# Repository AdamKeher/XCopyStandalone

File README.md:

# XCopy Standalone
An Arduino / Teensy based version of the Amiga XCopy application for copying floppy disks to and from ADF files. Built for the Teensy 3.2 using a custom PCB and an unmodified PC 3.5" floppy disk drive.

### Note
XCopy Standalone liberally uses floppy interface code taken from the excelent and generously open source ADF-Copy by Dominik Tonn. 
https://nickslabor.niteto.de/download/
Nicks software uses usb serial and a Java client or a MTP connection via usb to transfer data. XCopy Standalone focuses on a standalone unit using SD card storage and a LCD and / or web sockets interface for control.

### Thanks
Special thanks to Giants for all his help with this version including web interface graphics, documentation, suggestions etc.

## Device

## Status
This project is under heavy development and is in a state of flux with new hardware and software being actively worked on. The firmware version lives in `src/XCopy/XCopy.h`; this README describes v743.26.

## New Features - 09/2026

Since the 04/2023 release the device has grown a flux layer under the copier, a
second file system layer over the SD card, and a rebuilt web interface.

* **Disk Info** - a track analyser that describes what is on a disk rather than
  copying it. One pass per track, no retries, so a protected track with the wrong
  cylinder in its headers, a track with no sectors at all, or a disk with 84
  cylinders instead of 80 is the output rather than an error. Draws both surfaces
  as disks, a flux interval histogram per track, an angular track view you can
  point at, and the decoded sector under the pointer. Runs against the drive, or
  replays an SCP image through the same decoder.
* **Drive Toolkit** - a bench instrument for bringing up an unknown drive. Every
  interface line sampled with state, counts and rates; the safe outputs drivable
  one at a time, so a drive can be provoked into saying which fault it has; and a
  continuous head calibration read, after Amiga Test Kit's, that reports how many
  of the eleven sectors came back clean and whether the ones that did not came
  from the cylinder either side. Write data and write enable are deliberately not
  exposed.
* **SuperCard Pro flux images** - `readscp` captures a disk to an SCP file,
  streamed a block at a time because a single DD revolution is larger than the RAM
  on the whole part. A matching reader replays one back through the analyser.
* **Live USB flux streaming** - `live` hands the USB session to a host that does
  its own decoding, with non blocking in band seeking so the capture ring is still
  draining during a head move. Host side probe in `files/Tools/xcopylive_probe.py`.
* **ADF images as volumes** - mount ADF files as `ADF0:` and `ADF1:`, and the disk
  in the drive itself as `DF0:`, then use `dir`, `cat`, `cp`, `mkdir` and `rm`
  across the card and any mounted image. Mounts are read only unless asked
  otherwise. ADFlib upgraded to 0.10.7, with drivers rather than local edits.
* **New serial console** - a table driven interpreter with grouped help, per
  command options, tab completion and history, in place of the hand written parser.
* **Rebuilt web interface** - six tabs over one set of shared tokens and
  components, with the Disk Monitor histogram and the Disk Info analysis streamed
  to the browser as they are produced rather than gathered first.
* **Over the air updates** - firmware and web assets over Wi-Fi, no cable needed.
* **A name on the network** - the device calls itself `xcopy` to DHCP, to mDNS and
  to OTA.
* **Host side tests** - the `native` and `native_adf` environments run the file
  system and console tests off the board.

## New Features - 04/2023
* v0.19 PCB released with intergrated ESP8266 for WiFi
  * Moved to Kicad from Eagle
  * Changed SD Card to MicroSD reader
  * Added WiFi
  * Connected USB serial to Teensy USB serial
  * Moved TFT to cheap chinese Adafruit knock off, this has changed the pinout
    * https://www.aliexpress.com/item/4001144194129.html
    * USD $1.89!
  * Moved navigation stick to cheap chinese item from LCSC
  * Additional 3.3v power regulator to relieve Teensy's
  * Added larger electrolytic cap for floppy power
  * Switced to four layer board as they are cheap and provide better power / ground planes
* Project code moved from Arduino to ProjectIO with all libraries preinstalled
* New web interface
* Amiga module ripper
* Bootblock library / virus checker using brainfile format
* Web based disk monitor
* Network NTP time update
* Upload and download ADF files via web interface

## Features
* Software
  * Disk copy
    * Disk to SD Card
    * SD Card to Disk
    * Disk to Disk
    * Disk to Temporary Flash
    * Temporary Flash to Disk
  * Flux
    * Read a disk to a SuperCard Pro (SCP) flux image
    * Analyse a disk, or an SCP image, track by track
    * Flux interval histograms, per track and live during a copy
    * Stream a live drive to a host over USB for off board decoding
  * File systems
    * Amiga file system support for floppy disks and ADF files via ADFlib 0.10.7
    * Mount ADF images as `ADF0:` / `ADF1:`, and the disk in the drive as `DF0:`
    * List, print, copy, make and remove across the card and mounted images
  * Drive diagnostics
    * Every interface line sampled, with state, counts and rates
    * Individually drivable outputs for provoking a fault out of a drive
    * Continuous head calibration read with a live per cylinder tally
    * Drive speed from the index
  * Test disk
  * Format disk
  * Search a disk for case sensitive ascii text, or for tracker modules
  * Amiga module ripper
  * Bootblock library / virus checker using brainfile format
  * Serial command line, table driven, with tab completion and history
  * Interfaces
    * TFT LCD
    * USB Serial
    * HTML over WebSockets
  * Network
    * Over the air firmware and web asset updates
    * NTP time update and time zone
    * Announces itself as `xcopy` to DHCP, mDNS and OTA
  * Serial passthrough for programming onboard ESP8266
* Hardware
  * IDC 34 pin standard floppy drive cable interface
  * 1.8" ST7735R 128x160, 18bit color LCD
  * 5 way navigation joystick
  * Mono PAM8302 amplifier with adjustable Pot
    * Onboard mounted speaker
  * SD Card reader
  * 128MBit Flash Rom with built in ADF files
  * CR1220 battery backed realtime clock
  * ESP8266 for websockets driven interface
  * Single USB plug for serial and to power floppy and Teensy 3.2
  * Status LED's
  * Additional 3.3v power regulator
  * Gerbers, schematic and pcb layout files available 

# PCB

# Web Interface

Six tabs over one WebSocket connection to the ESP8266. The footer carries the
signal strength, the link state and what the device is doing, on every tab.

### Disk Copy

Every copy path in one place - between the drive, the SD card, the onboard flash,
and an ADF or SCP file on the card - over a live track map of both surfaces and a
rolling flux view of the track being read.

### Disk Monitor

A sector at a time: the decoded header, a hex dump, an ascii dump in either the
browser font or the Amiga one, and the track's flux histogram. Below them a block
scan of the whole disk, with ascii and tracker module searches, and blocks that
can be selected and written out to the card.

### Disk Info

The analyser. Both surfaces drawn as disks with every sector coloured by what was
found there, a status panel for the selected track, an angular track view of the
raw cell stream against the sectors decoded out of it, the flux histogram, and the
decoded sector under the pointer.

### Drive Toolkit

The drive itself rather than the disk in it. Sampled interface lines down the
left, the calibration read across the top, and a session tally that accumulates
per cylinder and head - so an intermittent read shows up as intermittent rather
than as one bad pass.

### SD Card

The contents of the card, with upload and download.

### Log

The serial console in the browser - the same interpreter, the same commands and
the same output as the USB port.

# Build Environment Notes:

## VSCode Plugins:
1. PlatoformIO with Teensy & ESP8266 board 
2. Todo+ v4.18.4 by Fabio Spampinato

* Xcopy.h contains PCBVERSION define to target firmware builds to different PCB versions

## ESP8266 Build Notes:
1. Select the `d1_mini` environment (both boards are environments of this one project)
2. Plugin XCopyStandalone device and select "Debugging >> ESP >> ESP Programming Mode"
3. Set serial port to the Teensy port, the device will passthrough serial data to the ESP8266 program
4. Upload code, then upload the web assets with the `d1_mini` "Build Filesystem Image" and "Upload Filesystem Image" tasks

### Over the air

Once the ESP is on your network it can be updated over Wi-Fi instead, using the
`d1_mini_ota` environment - both the firmware and the web assets:

```shell
pio run -e d1_mini_ota -t upload      # firmware
pio run -e d1_mini_ota -t uploadfs    # web interface
pio run -e d1_mini_ota -t uploadall   # both, firmware first
```

`uploadall` is a task of this project rather than of PlatformIO, and it waits
between the two because each upload reboots the ESP.

Use `uploadfs` for the web assets, not `uploadfsota`. The platform decides
whether espota is offering a sketch or a filesystem image by matching the target
name exactly, and `uploadfsota` misses that test - so the image goes over as a
sketch, is measured against the 1MB sketch region instead of its own 2MB
partition, and is refused with `ERROR[4]: Not Enough Space`. `scripts/
espota_fs_flag.py` puts the missing flag back, so both targets now work.

The device calls itself `xcopy` to the DHCP server, to mDNS and to OTA, so it is
reachable by whichever name your network gives it. `upload_port` in
`platformio.ini` is set to `xcopy.lab` - change it to `xcopy.local` to go via
mDNS instead, or to a bare IP address if neither resolves from your machine.

The serial passthrough above is unchanged and remains the way back in if an
update ever leaves the ESP unable to join a network.
5. Select "Debugging >> ESP >> Reset ESP"
6. Open a serial terminal
7. Connect to your wireless access point using the connect command
```shell
>> connect SSIDName Password
```
8. Type the following commands to confirm you have connected
```shell
>> status
WiFi Status: Connected
-----
Mode: STA
PHY mode: N
Channel: 10
AP id: 0
Status: 5
Auto connect: 1
SSID (6): SSIDName
Passphrase (12): Password
BSSID set: 0
>> ip
192.168.X.XX
>> ssid
SSIDName
>>
```

## Project layout

Both firmwares are environments of a single PlatformIO project, so the IDE lists
them in one Project Tasks tree and `pio run` with no arguments builds the pair.

| | |
|---|---|
| `src/` | Teensy 3.2 firmware, built by the `teensy31` environment |
| `src/esp8266/` | ESP8266 firmware, built by the `d1_mini` environment |
| `esp8266/data/` | web interface, uploaded to the ESP as a LittleFS image |
| `shared/` | the Teensy to ESP link contract, compiled into both |
| `lib/` | libraries for both; `esp8266/lib/` holds the ESP only ones |

Both boards are environments of the one project: `teensy31`, `d1_mini`, and
`d1_mini_ota` for updating the ESP over Wi-Fi. Two more, `native` and
`native_adf`, build nothing for a board and exist to run the console and file
system tests on the host.

Neither firmware is a `.ino` sketch: PlatformIO only converts a sketch sitting at
the top of the source directory, and with two source trees neither one can be.

## How to build PlatformIO based project

1. [Install PlatformIO Core](http://docs.platformio.org/page/core.html)
2. Download [development platform with examples](https://github.com/platformio/platform-teensy/archive/develop.zip)
3. Open the project
4. Pick the environment you want - `teensy31` or `d1_mini` - or build both at once
5. Select 'PlatformIO:Build'
6. Select 'PlatformIO:Upload'

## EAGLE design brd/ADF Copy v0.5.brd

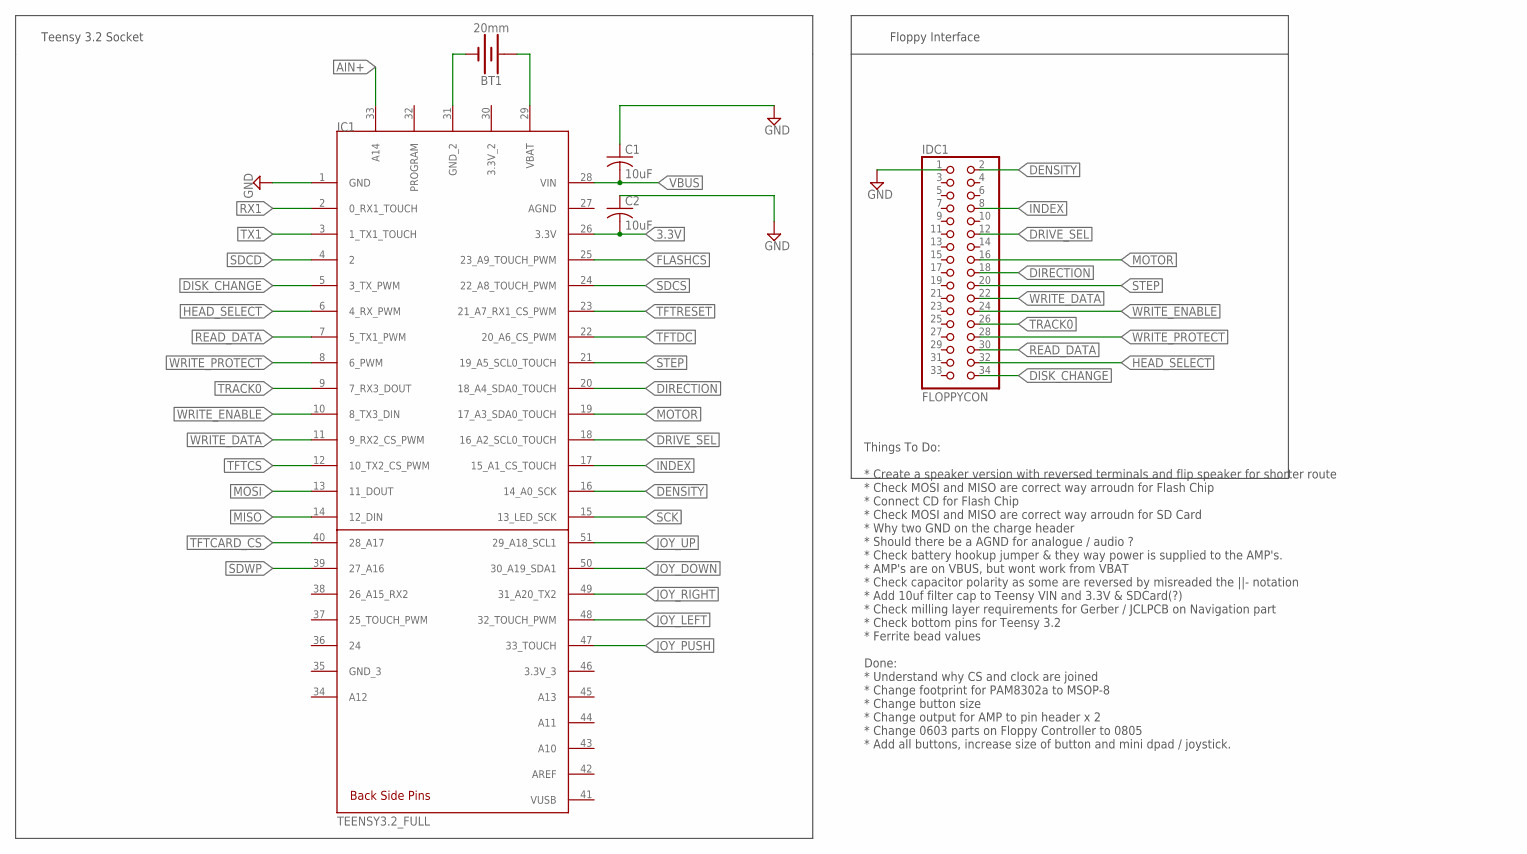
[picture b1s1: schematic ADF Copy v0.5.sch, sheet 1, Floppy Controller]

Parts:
BT1: 20mm; BATTCOM_20MM_PTH
C1, C2: 10uF; C0805
IC1: TEENSY3.2_FULL; DIP28X4-2.54-34.7X15.24MM
IDC1: FLOPPYCON; 2X17/90

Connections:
3.3V: C2.2, IC1.26 (3.3V); also elsewhere on the board
AIN+: IC1.33 (A14); also elsewhere on the board
DENSITY: IC1.16 (14_A0_SCK), IDC1.2
DIRECTION: IC1.20 (18_A4_SDA0_TOUCH), IDC1.18
DISK_CHANGE: IC1.5 (3_TX_PWM), IDC1.34
DRIVE_SEL: IC1.18 (16_A2_SCL0_TOUCH), IDC1.12
FLASHCS: IC1.25 (23_A9_TOUCH_PWM); also elsewhere on the board
GND: C1.1, C2.1, IC1.1 (GND), IDC1.1; also elsewhere on the board
HEAD_SELECT: IC1.6 (4_RX_PWM), IDC1.32
INDEX: IC1.17 (15_A1_CS_TOUCH), IDC1.8
JOY_DOWN: IC1.50 (30_A19_SDA1); also elsewhere on the board
JOY_LEFT: IC1.48 (32_TOUCH_PWM); also elsewhere on the board
JOY_PUSH: IC1.47 (33_TOUCH); also elsewhere on the board
JOY_RIGHT: IC1.49 (31_A20_TX2); also elsewhere on the board
JOY_UP: IC1.51 (29_A18_SCL1); also elsewhere on the board
MISO: IC1.14 (12_DIN); also elsewhere on the board
MOSI: IC1.13 (11_DOUT); also elsewhere on the board
MOTOR: IC1.19 (17_A3_SDA0_TOUCH), IDC1.16
unnamed: BT1.2 (-), IC1.31 (GND_2)
unnamed: BT1.1 (+), IC1.29 (VBAT)
READ_DATA: IC1.7 (5_TX1_PWM), IDC1.30
RX1: IC1.2 (0_RX1_TOUCH); also elsewhere on the board
SCK: IC1.15 (13_LED_SCK); also elsewhere on the board
SDCD: IC1.4 (2); also elsewhere on the board
SDCS: IC1.24 (22_A8_TOUCH_PWM); also elsewhere on the board
SDWP: IC1.39 (27_A16); also elsewhere on the board
STEP: IC1.21 (19_A5_SCL0_TOUCH), IDC1.20
TFTCARD_CS: IC1.40 (28_A17); also elsewhere on the board
TFTCS: IC1.12 (10_TX2_CS_PWM); also elsewhere on the board
TFTDC: IC1.22 (20_A6_CS_PWM); also elsewhere on the board
TFTRESET: IC1.23 (21_A7_RX1_CS_PWM); also elsewhere on the board
TRACK0: IC1.9 (7_RX3_DOUT), IDC1.26
TX1: IC1.3 (1_TX1_TOUCH); also elsewhere on the board
VBUS: C1.2, IC1.28 (VIN); also elsewhere on the board
WRITE_DATA: IC1.11 (9_RX2_CS_PWM), IDC1.22
WRITE_ENABLE: IC1.10 (8_TX3_DIN), IDC1.24
WRITE_PROTECT: IC1.8 (6_PWM), IDC1.28

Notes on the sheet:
Teensy 3.2 Socket
Things To Do: * Create a speaker version with reversed terminals and flip speaker for shorter route * Check MOSI and MISO are correct way arroudn for Flash Chip * Connect CD for Flash Chip * Check MOSI and MISO are correct way arroudn for SD Card * Why two GND on the charge header * Should there be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
Floppy Interface

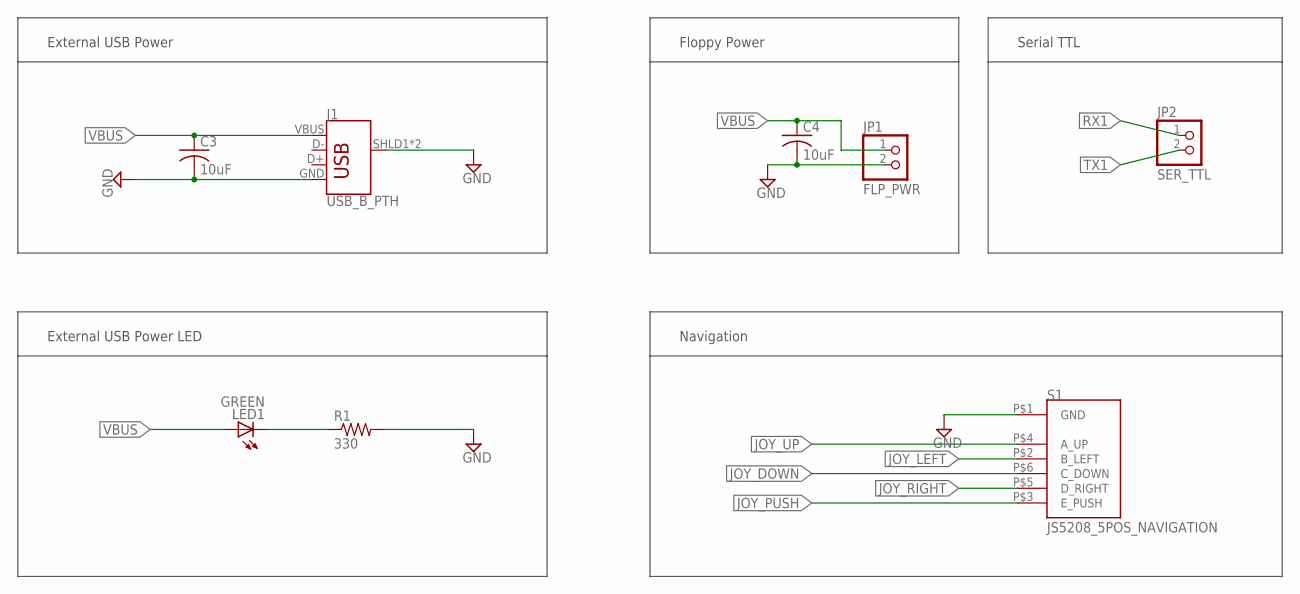
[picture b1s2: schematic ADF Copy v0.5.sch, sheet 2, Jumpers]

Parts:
C3, C4: 10uF; C0805
J1: USB_B_PTH; USB-B-PTH
JP1: FLP_PWR; 1X02
JP2: SER_TTL; 1X02
LED1: GREEN; CHIP-LED0805
R1: 330; R0805
S1: JS5208_5POS_NAVIGATION

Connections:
GND: C3.2, C4.2, J1.GND, J1.SHLD1 (SHIELD), J1.SHLD2 (SHIELD), JP1.2, R1.2, S1.P$1 (GND); also elsewhere on the board
JOY_DOWN: S1.P$6 (C_DOWN); also elsewhere on the board
JOY_LEFT: S1.P$2 (B_LEFT); also elsewhere on the board
JOY_PUSH: S1.P$3 (E_PUSH); also elsewhere on the board
JOY_RIGHT: S1.P$5 (D_RIGHT); also elsewhere on the board
JOY_UP: S1.P$4 (A_UP); also elsewhere on the board
unnamed: LED1.C, R1.1
RX1: JP2.1; also elsewhere on the board
TX1: JP2.2; also elsewhere on the board
VBUS: C3.1, C4.1, J1.VBUS, JP1.1, LED1.A; also elsewhere on the board

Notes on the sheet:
Serial TTL
Floppy Power
External USB Power
External USB Power LED
Navigation

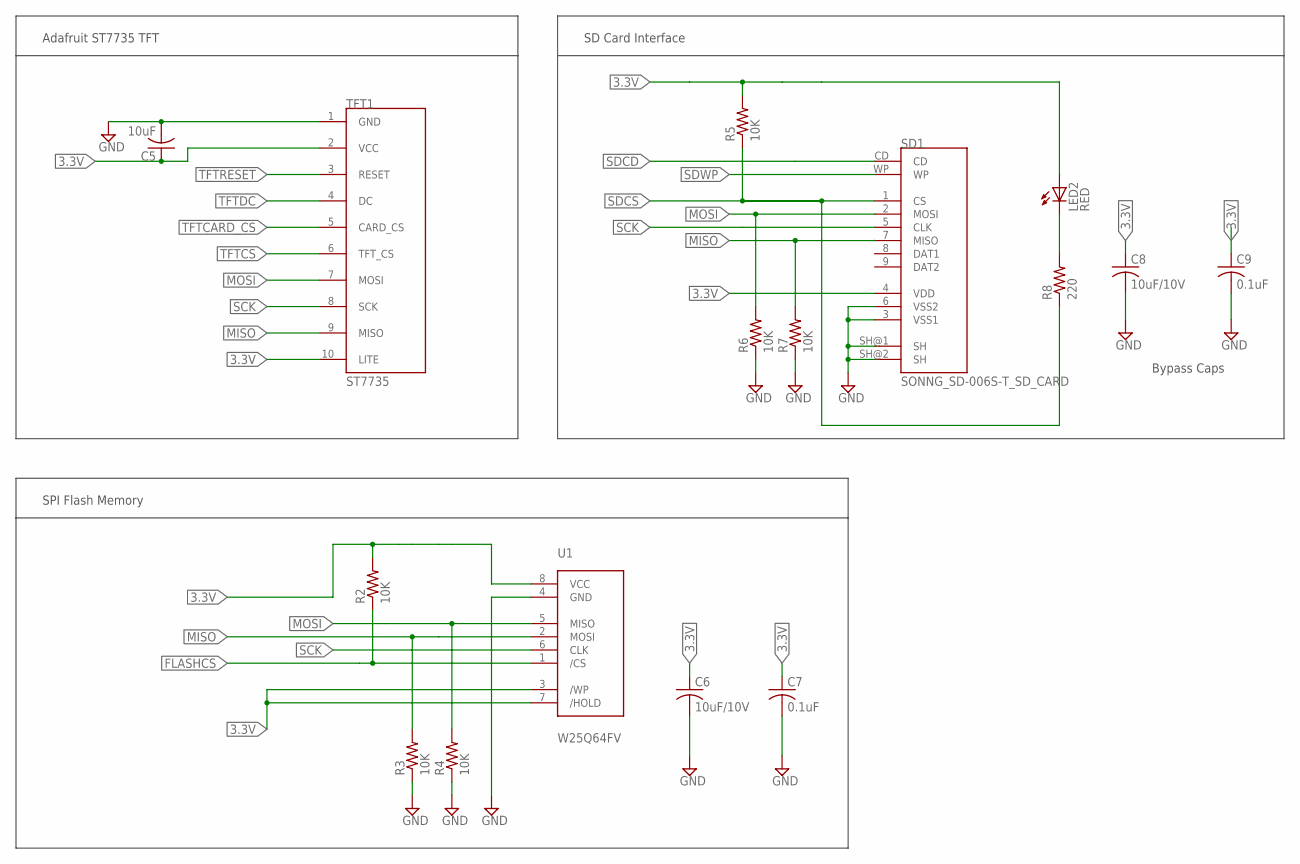
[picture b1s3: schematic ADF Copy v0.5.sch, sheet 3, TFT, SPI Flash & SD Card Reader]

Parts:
C5: 10uF; C0805
C6, C8: 10uF/10V; C0805
C7, C9: 0.1uF; C0805
LED2: RED; CHIP-LED0805
R2, R3, R4, R5, R6, R7: 10K; R0805
R8: 220; R0805
SD1: SONNG_SD-006S-T_SD_CARD; SD-006S-T
TFT1: ST7735
U1: W25Q64FV; SOIC8

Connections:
3.3V: C5.1, C6.1, C7.1, C8.1, C9.1, LED2.A, R2.2, R5.2, SD1.4 (VDD), TFT1.2 (VCC), TFT1.10 (LITE), U1.3 (/WP), U1.7 (/HOLD), U1.8 (VCC); also elsewhere on the board
FLASHCS: R2.1, U1.1 (/CS); also elsewhere on the board
GND: C5.2, C6.2, C7.2, C8.2, C9.2, R3.1, R4.1, R6.1, R7.1, SD1.3 (VSS1), SD1.6 (VSS2), SD1.SH@1 (SH), SD1.SH@2 (SH), TFT1.1 (GND), U1.4 (GND); also elsewhere on the board
MISO: R3.2, R7.2, SD1.7 (MISO), TFT1.9 (MISO), U1.2 (MOSI); also elsewhere on the board
MOSI: R4.2, R6.2, SD1.2 (MOSI), TFT1.7 (MOSI), U1.5 (MISO); also elsewhere on the board
unnamed: LED2.C, R8.2
SCK: SD1.5 (CLK), TFT1.8 (SCK), U1.6 (CLK); also elsewhere on the board
SDCD: SD1.CD; also elsewhere on the board
SDCS: R5.1, R8.1, SD1.1 (CS); also elsewhere on the board
SDWP: SD1.WP; also elsewhere on the board
TFTCARD_CS: TFT1.5 (CARD_CS); also elsewhere on the board
TFTCS: TFT1.6 (TFT_CS); also elsewhere on the board
TFTDC: TFT1.4 (DC); also elsewhere on the board
TFTRESET: TFT1.3 (RESET); also elsewhere on the board

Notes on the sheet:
Adafruit ST7735 TFT
SD Card Interface
Bypass Caps
SPI Flash Memory

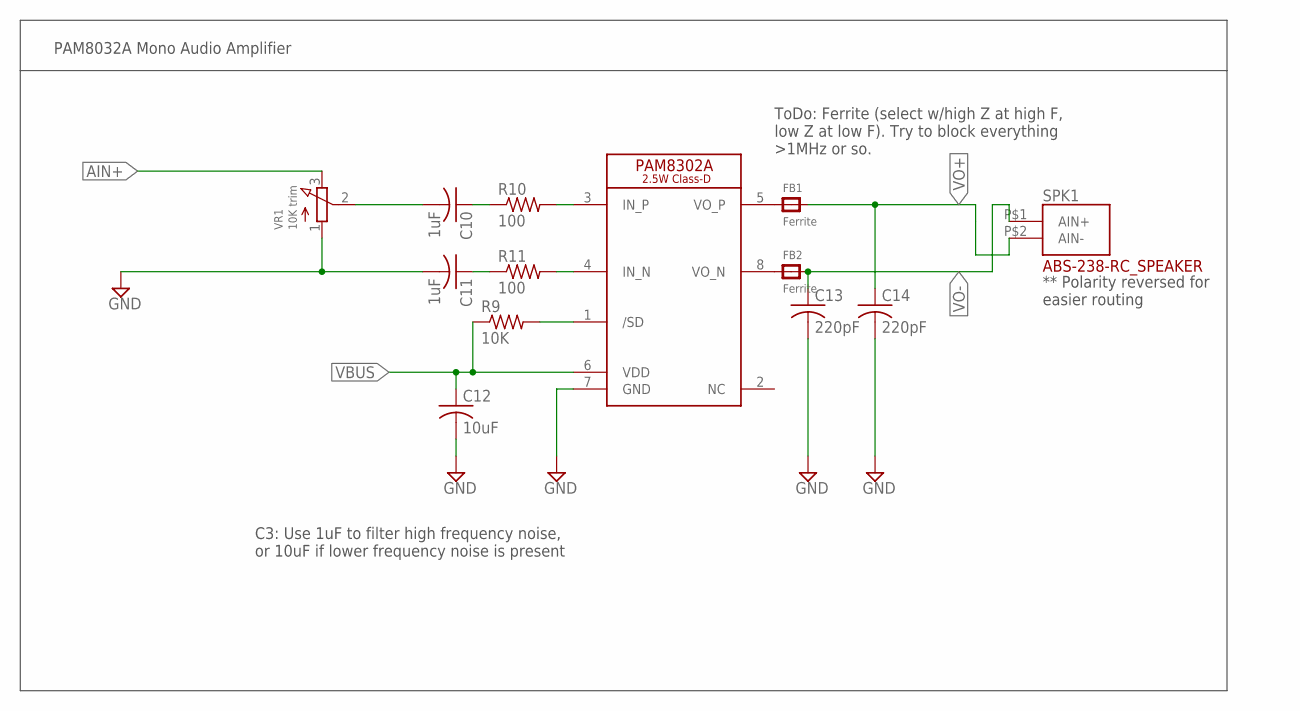
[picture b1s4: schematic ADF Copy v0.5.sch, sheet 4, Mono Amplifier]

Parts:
C10, C11: 1uF; C0805
C12: 10uF; C0805
C13, C14: 220pF; C0805
FB1, FB2: Ferrite; _0805
IC2: PAM8302A; SOIC8
R9: 10K; R0805
R10, R11: 100; R0805
SPK1: ABS-238-RC_SPEAKER
VR1: 10K trim; TRIMPOT_BOURNS_3303W

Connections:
AIN+: VR1.3 (E); also elsewhere on the board
GND: C11.2, C12.2, C13.2, C14.2, IC2.7 (GND), VR1.1 (A); also elsewhere on the board
unnamed: IC2.1 (/SD), R9.2
unnamed: FB1.1, IC2.5 (VO_P)
unnamed: FB2.1, IC2.8 (VO_N)
unnamed: IC2.4 (IN_N), R11.2
unnamed: IC2.3 (IN_P), R10.2
unnamed: C11.1, R11.1
unnamed: C10.1, R10.1
unnamed: C10.2, VR1.2 (S)
VBUS: C12.1, IC2.6 (VDD), R9.1; also elsewhere on the board
VO+: C14.1, FB1.2, SPK1.P$2 (AIN-)
VO-: C13.1, FB2.2, SPK1.P$1 (AIN+)

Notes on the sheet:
ToDo: Ferrite (select w/high Z at high F, low Z at low F). Try to block everything >1MHz or so.
C3: Use 1uF to filter high frequency noise, or 10uF if lower frequency noise is present
PAM8032A Mono Audio Amplifier
** Polarity reversed for easier routing

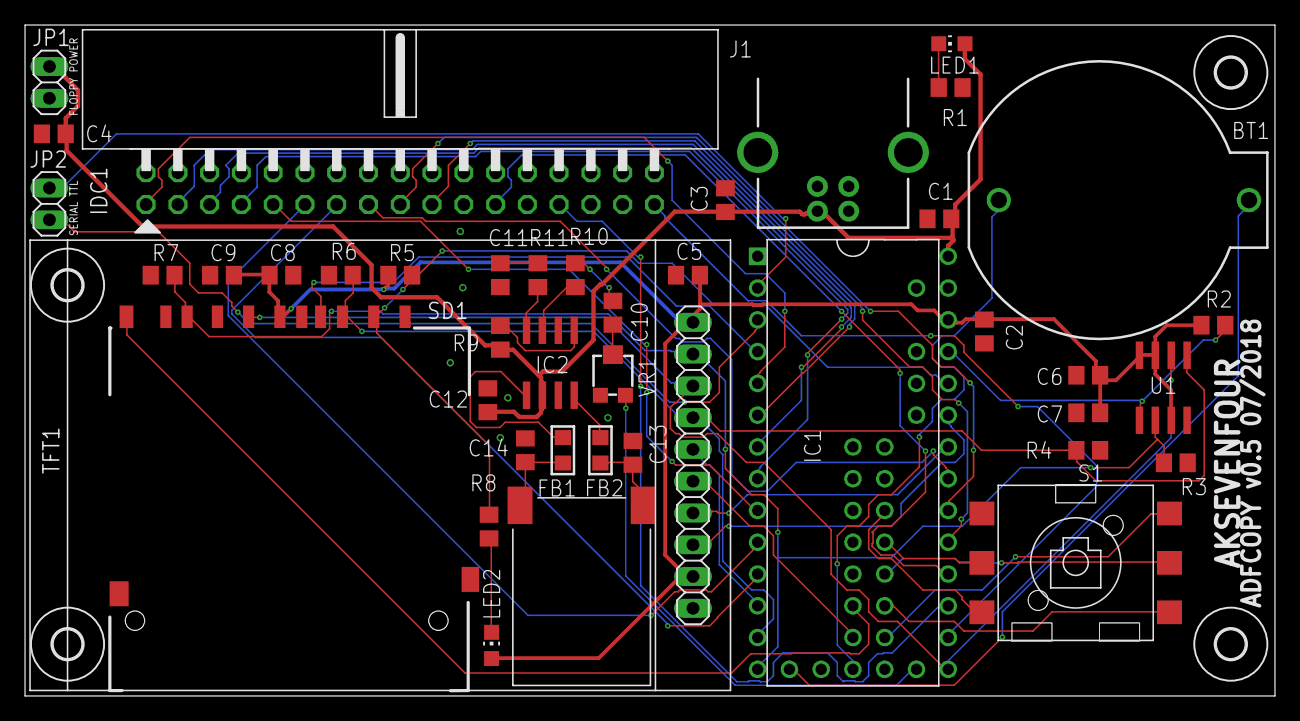
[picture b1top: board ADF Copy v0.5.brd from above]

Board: 2 copper layers, 99.9 x 53.6 mm, 46 parts (0 on the bottom side), 49 nets.

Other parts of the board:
U$1, U$2, U$3, U$4: M2_HOLE

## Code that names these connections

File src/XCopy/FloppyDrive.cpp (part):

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    registerSetup(1);
    pinMode(_dens, OUTPUT);
    digitalWriteFast(_dens, HIGH);
    pinMode(_index, INPUT_PULLUP);
    pinMode(_motor, OUTPUT);
    digitalWriteFast(_motor, HIGH);
    pinMode(_drivesel, OUTPUT);
    digitalWriteFast(_drivesel, HIGH);
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    digitalWriteFast(_writedata, HIGH);
    pinMode(_writeen, OUTPUT);
    digitalWriteFast(_writeen, HIGH);
    pinMode(_track0, INPUT_PULLUP);
    pinMode(_wprot, INPUT_PULLUP);
    pinMode(_side, OUTPUT);
    digitalWriteFast(_side, HIGH);
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        driveSelect();
        digitalWriteFast(_motor, LOW);
        motor = true;
        delay(600); // more than plenty of time to spinup motor
        if (autoDensity)
            initDrive();
    }
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
    if (version == 1)
    {
        _dens = 14;      //2 density select IN
        _index = 15;     //8 index OUT
        _drivesel = 16;  //12 drive select 1 IN
        _motor = 17;     //16 motor1 on IN
        _dir = 18;       //18 direction IN
        _step = 19;      //20 step IN
        _writedata = 9;  //22 write data IN
        _writeen = 8;    //24 write enable IN
        _track0 = 7;     //26 track 0 OUT
        _wprot = 6;      //28 write protect OUT
        _readdata = 5;   //30 read data OUT (FTM0_CH1) *** do not change this pin ***
        _side = 4;       //32 head select IN
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    }
    else
    {
        _dens = 2;        //2 density select IN
        _index = 3;       //8 index OUT
        _drivesel = 4;    //12 drive select 1 IN
        _motor = 5;       //16 motor1 on IN
        _dir = 6;         //18 direction IN
        _step = 7;        //20 step IN
        _writedata = 8;   //22 write data IN
        _writeen = 9;     //24 write enable IN
        _track0 = 10;     //26 track 0 OUT
        _wprot = 11;      //28 write protect OUT
        _readdata = 22;   //30 read data OUT (FTM0_CH1) *** do not change this pin ***
        _side = 14;       //32 head select IN
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
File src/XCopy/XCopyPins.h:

#ifndef XCOPYPINS_H
#define XCOPYPINS_H

#define PIN_SCLK  13  // SCLK can also use pin 14
#define PIN_MOSI  11  // MOSI can also use pin 7

#define PIN_DC    20   //  but certain pairs must NOT be used: 2+10, 6+9, 20+23, 21+22
#define PIN_RST   21   // RST can use any pinboot 
#define PIN_TFTCS 10 // CS & DC can use pins 2, 6, 9, 10, 15, 20, 21, 22, 23

#define PIN_FLASHCS         23
#define PIN_SDCS            22
#define PIN_BUSYPIN         24
#define PIN_ESPRESETPIN     25
#define PIN_ESPPROGPIN      26
#define PIN_TEENSYRESETPIN  28


#if PCBVERSION == 1
    #define PIN_NAVIGATION_UP_PIN    29
    #define PIN_NAVIGATION_DOWN_PIN  30
    #define PIN_NAVIGATION_RIGHT_PIN 31
    #define PIN_NAVIGATION_LEFT_PIN  32
    #define PIN_NAVIGATION_PUSH_PIN  33

    #define PIN_CARDWP               27
    #define PIN_CARDDETECT           2
#else
    #define PIN_NAVIGATION_UP_PIN    31
    #define PIN_NAVIGATION_DOWN_PIN  32
    #define PIN_NAVIGATION_RIGHT_PIN 29
    #define PIN_NAVIGATION_LEFT_PIN  30
    #define PIN_NAVIGATION_PUSH_PIN  33

    #define PIN_CARDWP               2
    #define PIN_CARDDETECT           27
#endif


#endif // XCOPYPINS_H

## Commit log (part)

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2022-04-06 Removed printDirectory and Added getFiles & getXFiles
2022-04-06 Added getSdFiles state
2022-04-06 Added updateWebSdCardFiles
2022-04-06 Added getSdFiles webCommand
2022-04-06 Updated web interface to support SD Card table
2022-04-06 Added printDirectory
2022-04-06 v708.2022
2022-04-06 Implementing SD Card subdirectories in the Web UI
2022-04-06 Updated SDCard on WebUI to support sub directories
2022-04-06 Fixed /sdcard path
2022-04-06 Rewrote directory handling routines
2022-04-06 Updated printDirectory for new SD Card code
2022-04-06 Updated directory handling routines
2022-04-06 Fixed adfToDisk when writing from SD Source
2022-04-06 Added pinout diagrams for Teensy & ESP
2022-04-07 File download stage 1
2022-04-07 Reduce delays as incrased serial baud
2022-04-07 Increased teensy to esp8266 baud: 115200 to 576000
2022-04-07 File download stage 2 - working but slow
2022-04-07 sendSize partly implemented
2022-04-07 clearwifi command added & skipped wifi connection if no ssid or password present.
2022-04-07 Cleaned up debug output for downloading files
2022-04-09 Fixed flux canvas width in webui
2022-04-09 Updated TODO
2022-04-09 Send size update
2022-04-09 Removed reduntant switch
2022-04-10 Change buffer size and disable content size
2022-04-10 Merged sendSize and sendFile commands
2022-04-10 Fixed http sendFile error handling
2022-04-10 Modified footer
2022-04-10 Set correct fluxCanvas size
2022-04-10 Flushed serial before sending from esp to teensy
2022-04-10 Url decode file paths
2022-04-10 Force vertical scrollbar
2022-04-10 Select tab on load based on url anchor
2022-04-10 Set url anchor on tab select
2022-04-10 Add favicon
2022-04-10 File selection dialog for Copy ADF to Disk
2022-04-10 Fixed file path in modal selection dialog
2022-04-10 Captured callback for writeADFFIle
2022-04-10 Hooked up writeADFFile to XCopyDIsk routines
2022-04-10 Changed file selection modal dialog width to large
2022-04-10 Removed test menu item
2022-04-10 Added font awesome icons
2022-04-10 Added refresh button to select modal dialog
2022-04-10 Updated WebUI ADF to Disk routines
2022-04-10 WebUI was not calling copyFlashToDisk
2022-04-10 Removed debug output
2022-04-10 Removed debug output from ADFlib for dump command
2022-04-11 Add cat command to dump files to terminal
2022-04-11 Added fileExists and deleteFile
2022-04-11 Added rm command to delete files from SD Card
2022-04-11 Added file upload handler
2022-04-11 Added rough upload form
2022-04-11 Added rough upload script
2022-04-11 Added rough getFile
2022-04-11 Update TODO
2022-04-13 File Upload updates
2022-04-13 Display flux when reading disk to ADF
2022-04-13 Link added to AK74 logo in footer
2022-04-13 Dimmed tabs in WebUI when device is busy
2022-04-13 Removed debug info
2022-04-13 Upload variables renamed
2022-04-13 Variable names fixed
2022-04-13 TODO Updated
2022-04-13 Removed redundant websocket onclose event
2022-04-13 Added ping command to websocket server
2022-04-13 Detect websocket disconnect and auto reconnect
2022-04-13 Clear disk on WebUI when starting disk flux
2022-04-14 Moved upload functions to upload.js
2022-04-14 Created upload.js & added fileUploadCancel()
2022-04-14 Added websocket command cancelUpload
2022-04-14 Send websocket command cancelUpload on upload error
2022-04-14 Moved error handling for SD card failures
2022-04-14 Include upload.js and cleanup upload error messages
2022-04-14 Added cancel button to file upload
2022-04-14 Improved websocket disconnection code
2022-04-14 Indicate on TFT when file transfer happening
2022-04-14 Added reconnect button to websocket disconnect modal
2022-04-14 Handle websocket timeout during file download
2022-04-14 Fixed menu.redraw() to print correct items
2022-04-14 Ported SPIFFS to LittleFS
2022-04-14 Set WebUI tab when starting activity from TFT
2022-04-14 Move CSS to Saas
2022-04-14 Updated track CSS and Sass
2022-04-15 Removed redundant xcopylogo CSS
2022-04-15 Renamed _main.scss to _xcopy.scss
2022-04-15 Restructured CSS
2022-04-15 Restructured Javascript
2022-04-15 Updated diskname in WebUI
2022-04-15 Added icons for mode and status
2022-04-15 Added white to .track
2022-04-15 Added .track.white
2022-04-15 Added track color key
2022-04-15 Added text parameter to setTrack
2022-04-15 Added table-sm key & changed track.white to whitesmoke
2022-04-15 Added .key class to key
2022-04-15 Updated readTrack & writeTrack to display errors
2022-04-15 Increased websocket ping timeout from 1 to 3 sec
2022-04-15 Updated disk activity key to save vertical space
2022-04-15 Fixed bottom margin for key
2022-04-15 Updated margins.
2022-04-15 Updated white space
2022-04-16 diskToADF step #1
2022-04-16 Added print function to output directly to Serial1
2022-04-16 DiskFlux display fix
2022-04-16 Added generateADFFileName
2022-04-16 Added makeDirectory & getSdFat
2022-04-16 Move XCopyDisk SD card routines to XCopySDCard
2022-04-16 Add md5 hash command
2022-04-16 Removed white space
2022-04-16 Removed cardDetect(), add MD5 & create _sdcard
2022-04-16 Reduced XCopyDirectory mem footprint - still sucks
2022-04-17 Removed path to reduce memory footprint
2022-04-18 Added write <adffile> to cmdline
2022-04-18 Add xcopy callback to cmdline obj and testdisk cmd
2022-04-18 Added md5 to diskcheck
2022-04-19 Set mode width in WebUI
2022-04-19 Added MD5 to verify data for adfToDisk
2022-04-19 writeadf command updated to use callback
2022-04-20 Added ctxToMD5
2022-04-20 Added XCopyDisk::adfToMD5
2022-04-20 added XCopyDisk::flashToMD5 and 'md5 flash' to cmdline
2022-04-20 Updated help
2022-04-20 Display MD5 for DiskToFlash
2022-04-20 Added writeflash to cmdline
2022-04-20 Added delay to XCopyLog and used _esp->print
2022-04-20 Fixed bug in log output with commas
2022-04-20 Added XCopyLog and updated printBootSector()
2022-04-20 Updated cat command to log to WebUI
2022-04-20 Updated log creation
2022-04-24 Added processKey & processKeys
2022-04-24 Added onKey event handler to xterm.js to capture keyboard input
2022-04-24 Added procesKeys method and processed key command from esp.
2022-04-24 Added backspace
2022-04-24 Blocked cursor keys from WebUI console
2022-04-24 Updated md5 command to output to WebUI
2022-04-25 Fixed compiler warnings
2022-04-25 Fixed busy state in WebUI
2022-04-25 Added setbusy web command
2022-04-25 Added hardwareStatus and don't ping when busy
2022-04-26 Updated dumpConfig to output to WebUI
2022-04-26 Fixed read command to output to WebUI
2022-04-26 Updated hist command to output to WebUI
2022-04-26 Fixed print command to output to WebUI
2022-04-26 Fixed dump command to output to WebUI
2022-04-27 Updated XCopyESP8266 sendCommand
2022-04-27 Added busy state to ls / dir
2022-04-27 Added cancel button to WebUI. Requires hardware modification.
2022-04-27 Adjusted spacing under Cancel button
2022-04-27 Detect presence of cancel wire
2022-05-01 WebUI Diskview - stage 1
2022-05-01 Added 'pass' command to enter ESP passthrough mode
2022-05-01 Added track info to Disk View
2022-05-01 Added more track info to Disk View
2022-05-02 Direct input of track / sector / side for Disk View
2022-05-02 Highlight ascii value on hover over hex in Disk View
2022-05-02 Added histogram to Disk View
2022-05-02 Remove redundant information from Disk View
2022-05-02 Updated pin out image
2022-05-03 Added initial hex and ascii dump data
2022-05-03 Disk View updates existing divs for hex and ascii dump to make page static
2022-05-03 Updated Disk View CSS
2022-05-03 Added space under histogram
2022-05-03 Added warning to sd card upload function
2022-05-03 Updated Disk View layout
2022-05-03 Change timing of histogram drawing
2022-05-03 Update Disk View icons
2022-05-04 Updated WebUI mode, button status & icons
2022-05-04 Removed default argument from diskToADF & adfToDisk
2022-05-04 Fixed Disk to Disk WebUI mode & state
2022-05-04 Updated Disk View ASCII dump to use Amiga Topaz font
2022-05-04 Updated ASCII dump
2022-05-04 Updated ASCII Dump icon
2022-05-05 Updated Disk View dump views
2022-05-05 Fixed overflow issue
2022-05-05 Added Empty Blocks html
2022-05-05 Added resetEmptyBlocks and setEmptyBlock
2022-05-05 Added websocket commands resetEmptyBlocks & setEmptyBlock
2022-05-05 Scan Empty Blocks - Step 1
2022-05-05 Scan Empty Blocks - Step 2
2022-05-05 Scan Empty Blocks - Step 3
2022-05-05 Scan Empty Blocks - Step 4
2022-05-06 Scan Empty Blocks - Step 5
2022-05-07 Added clear blocks and highlighted current block in empty blocks
2022-05-07 Renamed Empty Blocks to Disk Usage
2022-05-07 Fixed block highlight is Disk Usage
2022-05-08 ASCII Search - Stage 1
2022-05-09 ASCII Search - Stage 2
2022-05-09 Added asciiSearch
2022-05-09 Moved console ouput
2022-05-09 ASCII Search - Stage 3
2022-05-09 ASCII Search - Stage 4
2022-05-09 Add cancelled message to Ascii Search
2022-05-09 Added writebin command
2022-05-09 Updated scanblocks output to show ansi color results in console
2022-05-09 Updated writebin TFT & WebUI output
2022-05-09 Removed debug output from ls command
2022-05-10 Changed track to logical track in printAmigaSector
2022-05-11 Mod Search - Stage 1
2022-05-11 Mod Search - Stage 2
2022-05-11 Added 'modsearch' command to help text
2022-05-11 Mod Search - Stage 3
2022-05-11 Add 'Mod Search' button to 'Disk View'
2022-05-11 Updated search output
2022-05-12 Update modsearch output
2022-05-12 Highlight searchmod blocks on 'Disk View'
2022-05-12 Update byte2char to have optional delimiter
2022-05-12 Updated modsearch processing
2022-05-12 Fixed pattern output in Print()
2022-05-13 ModRip - Stage 1
2022-05-13 Mod Rip - Stage 2
2022-05-13 ModRip - Stage 2
2022-05-13 Added check for search parameter
2022-05-13 Documentation
2022-05-13 Fixed block highlight in Disk View for ASCII search
2022-05-13 Added memory addresses to Header Dump on ModInfo Print
2022-05-13 Modified example command output for processModule
2022-05-14 Updated modsearch command to locate several different trackers
2022-05-14 Updated documentation
2022-05-16 Updated DiskLocation object and fixed modsearch command
2022-05-16 Added Doxyfile
2022-05-16 Replaced depricated JsonObject asString() method with as<char*>()
2022-05-16 Fixed string & char* error
2022-05-16 Removed debug info and fixed NULL comparison warning
2022-05-16 Fixed sprinf formating warnings
2022-05-16 Fixed issue with default param for Byte2Char
2022-05-16 Fixed compilation warnings for sprintf
2022-05-16 Fixed const char* conversion warning
2022-05-16 Removed unused variables
2022-05-16 Renamed timer
2022-05-20 Rename Disk View to Disk Monitor and start Disk Info
2022-05-20 Update ArduinoJson
2022-05-20 Move StaticJsonBuffer to StaticJsonDocument and updte serialisation routines.
2022-05-20 Add CRC32 to boot block output
2022-05-20 Move StaticJsonBuffer to StaticJsonDocument and update serialisation routines
2022-05-20 Added function to return CRC32 for boot block
2022-05-20 Added brainfile.json
2022-05-20 Added class to indentify bootblock using brainfile.json
2022-05-20 Added boot block identification to 'boot' command
2022-05-20 Updated to read brainfile.json from Flash Memory
2022-05-20 Check for brain file whe starting
2022-05-20 Added crass demo as test data
2022-05-20 Added identification method
2022-05-20 Fixed CRC32 output
2022-05-20 Updated CRC32 output
2023-04-16 Updated for new PCB version
2023-04-16 Add board photo
2023-04-16 Add PCB Image
2023-04-16 Updatge README
2023-04-16 Added schematic
2023-04-16 Updated schematic
2023-04-16 Removed TFT zip
2023-04-16 Added case
2023-04-17 Add card insert and eject audio feedback
2023-04-17 Updated Images

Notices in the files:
src/XCopy/FloppyDrive.cpp:
partly based on DecodeSectorData and DecodeLongword from AFR.C, written by
Marco Veneri Copyright (C) 1997 released as public domain
parts and their libraries:
microbuilder: This work is placed in the public domain, and may be freely used for commercial and non-commercial work with the following conditions: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
SparkFun-Connectors: Licensing: Creative Commons ShareAlike 4.0 International - https://creativecommons.org/licenses/by-sa/4.0
